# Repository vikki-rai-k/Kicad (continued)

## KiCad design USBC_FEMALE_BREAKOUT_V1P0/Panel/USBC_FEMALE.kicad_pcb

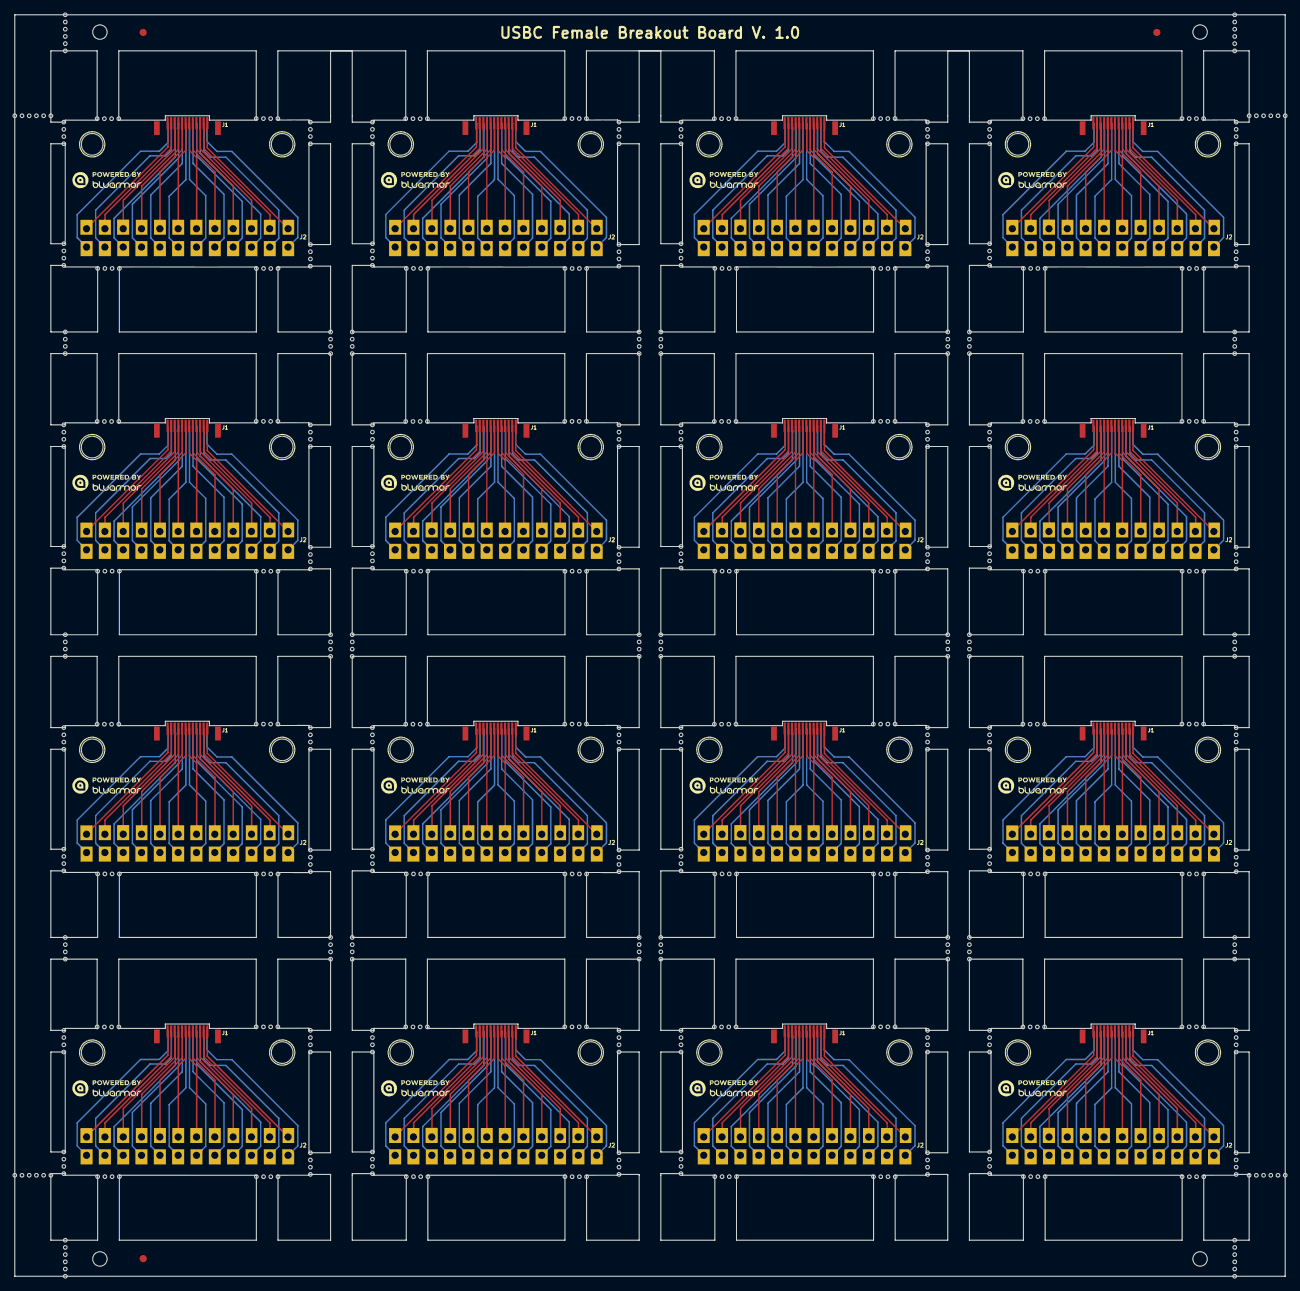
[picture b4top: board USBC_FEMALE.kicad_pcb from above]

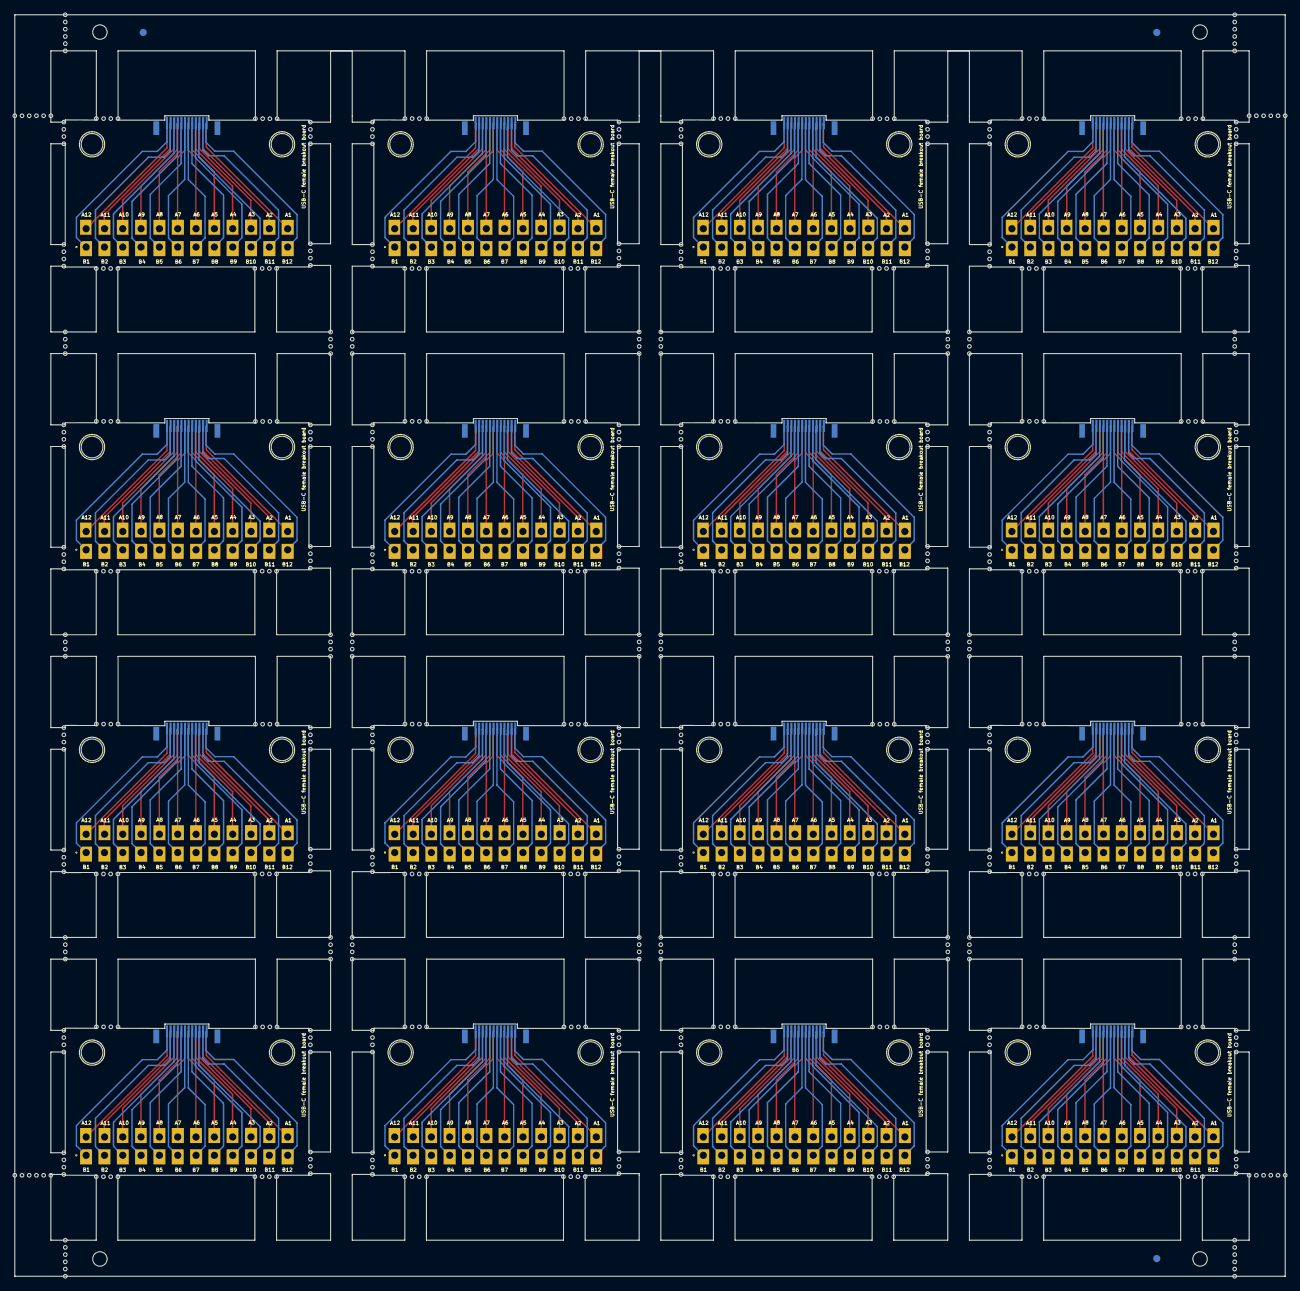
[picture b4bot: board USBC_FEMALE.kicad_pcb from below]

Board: 2 copper layers, 176.1 x 174.9 mm, 730 parts (19 on the bottom side), 384 nets.

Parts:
H1, H1#2, H1#3, H1#4, H1#5, H1#6, H1#7, H1#8, H1#9, H1#10, H1#11, H1#12, H1#13, H1#14, H1#15, H1#16, H2, H2#2, H2#3, H2#4, H2#5, H2#6, H2#7, H2#8, H2#9, H2#10, H2#11, H2#12, H2#13, H2#14, H2#15, H2#16: MountingHoleCircle; MountingHole_Circle_3.0mm
J1, J1#2, J1#3, J1#4, J1#5, J1#6, J1#7, J1#8, J1#9, J1#10, J1#11, J1#12, J1#13, J1#14, J1#15, J1#16: 2305018-2; SHOUHAN 24PIN 0.8 L9.3 027
J2, J2#2, J2#3, J2#4, J2#5, J2#6, J2#7, J2#8, J2#9, J2#10, J2#11, J2#12, J2#13, J2#14, J2#15, J2#16: Conn_01x24; M20-97412XX_large_pads
KiKit_FID_B_1, KiKit_FID_B_2, KiKit_FID_B_3: Fiducial
KiKit_FID_T_1, KiKit_FID_T_2, KiKit_FID_T_3: Fiducial
KiKit_MB_1_1, KiKit_MB_1_2, KiKit_MB_1_3, KiKit_MB_1_4, KiKit_MB_2_1, KiKit_MB_2_2, KiKit_MB_2_3, KiKit_MB_2_4, KiKit_MB_3_1, KiKit_MB_3_2, KiKit_MB_3_3, KiKit_MB_3_4, KiKit_MB_4_1, KiKit_MB_4_2, KiKit_MB_4_3, KiKit_MB_4_4, KiKit_MB_5_1, KiKit_MB_5_2, KiKit_MB_5_3, KiKit_MB_5_4, KiKit_MB_6_1, KiKit_MB_6_2, KiKit_MB_6_3, KiKit_MB_6_4, KiKit_MB_7_1, KiKit_MB_7_2, KiKit_MB_7_3, KiKit_MB_7_4, KiKit_MB_8_1, KiKit_MB_8_2, KiKit_MB_8_3, KiKit_MB_8_4, KiKit_MB_9_1, KiKit_MB_9_2, KiKit_MB_9_3, KiKit_MB_9_4, KiKit_MB_10_1, KiKit_MB_10_2, KiKit_MB_10_3, KiKit_MB_10_4, KiKit_MB_11_1, KiKit_MB_11_2, KiKit_MB_11_3, KiKit_MB_11_4, KiKit_MB_12_1, KiKit_MB_12_2, KiKit_MB_12_3, KiKit_MB_12_4, KiKit_MB_13_1, KiKit_MB_13_2, KiKit_MB_13_3, KiKit_MB_13_4, KiKit_MB_14_1, KiKit_MB_14_2, KiKit_MB_14_3, KiKit_MB_14_4, KiKit_MB_15_1, KiKit_MB_15_2, KiKit_MB_15_3, KiKit_MB_15_4, KiKit_MB_16_1, KiKit_MB_16_2, KiKit_MB_16_3, KiKit_MB_16_4, KiKit_MB_17_1, KiKit_MB_17_2, KiKit_MB_17_3, KiKit_MB_17_4, KiKit_MB_18_1, KiKit_MB_18_2, KiKit_MB_18_3, KiKit_MB_18_4, KiKit_MB_19_1, KiKit_MB_19_2, KiKit_MB_19_3, KiKit_MB_19_4, KiKit_MB_20_1, KiKit_MB_20_2, KiKit_MB_20_3, KiKit_MB_20_4, KiKit_MB_21_1, KiKit_MB_21_2, KiKit_MB_21_3, KiKit_MB_21_4, KiKit_MB_22_1, KiKit_MB_22_2, KiKit_MB_22_3, KiKit_MB_22_4, KiKit_MB_23_1, KiKit_MB_23_2, KiKit_MB_23_3, KiKit_MB_23_4, KiKit_MB_24_1, KiKit_MB_24_2, KiKit_MB_24_3, KiKit_MB_24_4, KiKit_MB_25_1, KiKit_MB_25_2, KiKit_MB_25_3, KiKit_MB_25_4, KiKit_MB_26_1, KiKit_MB_26_2, KiKit_MB_26_3, KiKit_MB_26_4, KiKit_MB_27_1, KiKit_MB_27_2, KiKit_MB_27_3, KiKit_MB_27_4, KiKit_MB_28_1, KiKit_MB_28_2, KiKit_MB_28_3, KiKit_MB_28_4, KiKit_MB_29_1, KiKit_MB_29_2, KiKit_MB_29_3, KiKit_MB_29_4, KiKit_MB_30_1, KiKit_MB_30_2, KiKit_MB_30_3, KiKit_MB_30_4, KiKit_MB_31_1, KiKit_MB_31_2, KiKit_MB_31_3, KiKit_MB_31_4, KiKit_MB_32_1, KiKit_MB_32_2, KiKit_MB_32_3, KiKit_MB_32_4, KiKit_MB_33_1, KiKit_MB_33_2, KiKit_MB_33_3, KiKit_MB_33_4, KiKit_MB_34_1, KiKit_MB_34_2, KiKit_MB_34_3, KiKit_MB_34_4, KiKit_MB_35_1, KiKit_MB_35_2, KiKit_MB_35_3, KiKit_MB_35_4, KiKit_MB_36_1, KiKit_MB_36_2, KiKit_MB_36_3, KiKit_MB_36_4, KiKit_MB_37_1, KiKit_MB_37_2, KiKit_MB_37_3, KiKit_MB_37_4, KiKit_MB_38_1, KiKit_MB_38_2, KiKit_MB_38_3, KiKit_MB_38_4, KiKit_MB_39_1, KiKit_MB_39_2, KiKit_MB_39_3, KiKit_MB_39_4, KiKit_MB_40_1, KiKit_MB_40_2, KiKit_MB_40_3, KiKit_MB_40_4, KiKit_MB_41_1, KiKit_MB_41_2, KiKit_MB_41_3, KiKit_MB_41_4, KiKit_MB_42_1, KiKit_MB_42_2, KiKit_MB_42_3, KiKit_MB_42_4, KiKit_MB_43_1, KiKit_MB_43_2, KiKit_MB_43_3, KiKit_MB_43_4, KiKit_MB_44_1, KiKit_MB_44_2, KiKit_MB_44_3, KiKit_MB_44_4, KiKit_MB_45_1, KiKit_MB_45_2, KiKit_MB_45_3, KiKit_MB_45_4, KiKit_MB_46_1, KiKit_MB_46_2, KiKit_MB_46_3, KiKit_MB_46_4, KiKit_MB_47_1, KiKit_MB_47_2, KiKit_MB_47_3, KiKit_MB_47_4, KiKit_MB_48_1, KiKit_MB_48_2, KiKit_MB_48_3, KiKit_MB_48_4, KiKit_MB_49_1, KiKit_MB_49_2, KiKit_MB_49_3, KiKit_MB_49_4, KiKit_MB_50_1, KiKit_MB_50_2, KiKit_MB_50_3, KiKit_MB_50_4, KiKit_MB_51_1, KiKit_MB_51_2, KiKit_MB_51_3, KiKit_MB_51_4, KiKit_MB_52_1, KiKit_MB_52_2, KiKit_MB_52_3, KiKit_MB_52_4, KiKit_MB_53_1, KiKit_MB_53_2, KiKit_MB_53_3, KiKit_MB_53_4, KiKit_MB_54_1, KiKit_MB_54_2, KiKit_MB_54_3, KiKit_MB_54_4, KiKit_MB_55_1, KiKit_MB_55_2, KiKit_MB_55_3, KiKit_MB_55_4, KiKit_MB_56_1, KiKit_MB_56_2, KiKit_MB_56_3, KiKit_MB_56_4, KiKit_MB_57_1, KiKit_MB_57_2, KiKit_MB_57_3, KiKit_MB_57_4, KiKit_MB_58_1, KiKit_MB_58_2, KiKit_MB_58_3, KiKit_MB_58_4, KiKit_MB_59_1, KiKit_MB_59_2, KiKit_MB_59_3, KiKit_MB_59_4, KiKit_MB_60_1, KiKit_MB_60_2, KiKit_MB_60_3, KiKit_MB_60_4, KiKit_MB_61_1, KiKit_MB_61_2, KiKit_MB_61_3, KiKit_MB_61_4, KiKit_MB_62_1, KiKit_MB_62_2, KiKit_MB_62_3, KiKit_MB_62_4, KiKit_MB_63_1, KiKit_MB_63_2, KiKit_MB_63_3, KiKit_MB_63_4, KiKit_MB_64_1, KiKit_MB_64_2, KiKit_MB_64_3, KiKit_MB_64_4, KiKit_MB_65_1, KiKit_MB_65_2, KiKit_MB_65_3, KiKit_MB_65_4, KiKit_MB_66_1, KiKit_MB_66_2, KiKit_MB_66_3, KiKit_MB_66_4, KiKit_MB_67_1, KiKit_MB_67_2, KiKit_MB_67_3, KiKit_MB_67_4, KiKit_MB_68_1, KiKit_MB_68_2, KiKit_MB_68_3, KiKit_MB_68_4, KiKit_MB_69_1, KiKit_MB_69_2, KiKit_MB_69_3, KiKit_MB_69_4, KiKit_MB_70_1, KiKit_MB_70_2, KiKit_MB_70_3, KiKit_MB_70_4, KiKit_MB_71_1, KiKit_MB_71_2, KiKit_MB_71_3, KiKit_MB_71_4, KiKit_MB_72_1, KiKit_MB_72_2, KiKit_MB_72_3, KiKit_MB_72_4, KiKit_MB_73_1, KiKit_MB_73_2, KiKit_MB_73_3, KiKit_MB_73_4, KiKit_MB_74_1, KiKit_MB_74_2, KiKit_MB_74_3, KiKit_MB_74_4, KiKit_MB_75_1, KiKit_MB_75_2, KiKit_MB_75_3, KiKit_MB_75_4, KiKit_MB_76_1, KiKit_MB_76_2, KiKit_MB_76_3, KiKit_MB_76_4, KiKit_MB_77_1, KiKit_MB_77_2, KiKit_MB_77_3, KiKit_MB_77_4, KiKit_MB_78_1, KiKit_MB_78_2, KiKit_MB_78_3, KiKit_MB_78_4, KiKit_MB_79_1, KiKit_MB_79_2, KiKit_MB_79_3, KiKit_MB_79_4, KiKit_MB_80_1, KiKit_MB_80_2, KiKit_MB_80_3, KiKit_MB_80_4, KiKit_MB_81_1, KiKit_MB_81_2, KiKit_MB_81_3, KiKit_MB_81_4, KiKit_MB_82_1, KiKit_MB_82_2, KiKit_MB_82_3, KiKit_MB_82_4, KiKit_MB_83_1, KiKit_MB_83_2, KiKit_MB_83_3, KiKit_MB_83_4, KiKit_MB_84_1, KiKit_MB_84_2, KiKit_MB_84_3, KiKit_MB_84_4, KiKit_MB_85_1, KiKit_MB_85_2, KiKit_MB_85_3, KiKit_MB_85_4, KiKit_MB_86_1, KiKit_MB_86_2, KiKit_MB_86_3, KiKit_MB_86_4, KiKit_MB_87_1, KiKit_MB_87_2, KiKit_MB_87_3, KiKit_MB_87_4, KiKit_MB_88_1, KiKit_MB_88_2, KiKit_MB_88_3, KiKit_MB_88_4, KiKit_MB_89_1, KiKit_MB_89_2, KiKit_MB_89_3, KiKit_MB_89_4, KiKit_MB_90_1, KiKit_MB_90_2, KiKit_MB_90_3, KiKit_MB_90_4, KiKit_MB_91_1, KiKit_MB_91_2, KiKit_MB_91_3, KiKit_MB_91_4, KiKit_MB_92_1, KiKit_MB_92_2, KiKit_MB_92_3, KiKit_MB_92_4, KiKit_MB_93_1, KiKit_MB_93_2, KiKit_MB_93_3, KiKit_MB_93_4, KiKit_MB_94_1, KiKit_MB_94_2, KiKit_MB_94_3, KiKit_MB_94_4, KiKit_MB_95_1, KiKit_MB_95_2, KiKit_MB_95_3, KiKit_MB_95_4, KiKit_MB_96_1, KiKit_MB_96_2, KiKit_MB_96_3, KiKit_MB_96_4, KiKit_MB_97_1, KiKit_MB_97_2, KiKit_MB_97_3, KiKit_MB_97_4, KiKit_MB_98_1, KiKit_MB_98_2, KiKit_MB_98_3, KiKit_MB_98_4, KiKit_MB_99_1, KiKit_MB_99_2, KiKit_MB_99_3, KiKit_MB_99_4, KiKit_MB_100_1, KiKit_MB_100_2, KiKit_MB_100_3, KiKit_MB_100_4, KiKit_MB_101_1, KiKit_MB_101_2, KiKit_MB_101_3, KiKit_MB_101_4, KiKit_MB_102_1, KiKit_MB_102_2, KiKit_MB_102_3, KiKit_MB_102_4, KiKit_MB_103_1, KiKit_MB_103_2, KiKit_MB_103_3, KiKit_MB_103_4, KiKit_MB_104_1, KiKit_MB_104_2, KiKit_MB_104_3, KiKit_MB_104_4, KiKit_MB_105_1, KiKit_MB_105_2, KiKit_MB_105_3, KiKit_MB_105_4, KiKit_MB_106_1, KiKit_MB_106_2, KiKit_MB_106_3, KiKit_MB_106_4, KiKit_MB_107_1, KiKit_MB_107_2, KiKit_MB_107_3, KiKit_MB_107_4, KiKit_MB_108_1, KiKit_MB_108_2, KiKit_MB_108_3, KiKit_MB_108_4, KiKit_MB_109_1, KiKit_MB_109_2, KiKit_MB_109_3, KiKit_MB_109_4, KiKit_MB_110_1, KiKit_MB_110_2, KiKit_MB_110_3, KiKit_MB_110_4, KiKit_MB_111_1, KiKit_MB_111_2, KiKit_MB_111_3, KiKit_MB_111_4, KiKit_MB_112_1, KiKit_MB_112_2, KiKit_MB_112_3, KiKit_MB_112_4, KiKit_MB_113_1, KiKit_MB_113_2, KiKit_MB_113_3, KiKit_MB_113_4, KiKit_MB_114_1, KiKit_MB_114_2, KiKit_MB_114_3, KiKit_MB_114_4, KiKit_MB_115_1, KiKit_MB_115_2, KiKit_MB_115_3, KiKit_MB_115_4, KiKit_MB_116_1, KiKit_MB_116_2, KiKit_MB_116_3, KiKit_MB_116_4, KiKit_MB_117_1, KiKit_MB_117_2, KiKit_MB_117_3, KiKit_MB_117_4, KiKit_MB_118_1, KiKit_MB_118_2, KiKit_MB_118_3, KiKit_MB_118_4, KiKit_MB_119_1, KiKit_MB_119_2, KiKit_MB_119_3, KiKit_MB_119_4, KiKit_MB_120_1, KiKit_MB_120_2, KiKit_MB_120_3, KiKit_MB_120_4, KiKit_MB_121_1, KiKit_MB_121_2, KiKit_MB_121_3, KiKit_MB_121_4, KiKit_MB_122_1, KiKit_MB_122_2, KiKit_MB_122_3, KiKit_MB_122_4, KiKit_MB_123_1, KiKit_MB_123_2, KiKit_MB_123_3, KiKit_MB_123_4, KiKit_MB_124_1, KiKit_MB_124_2, KiKit_MB_124_3, KiKit_MB_124_4, KiKit_MB_125_1, KiKit_MB_125_2, KiKit_MB_125_3, KiKit_MB_125_4, KiKit_MB_126_1, KiKit_MB_126_2, KiKit_MB_126_3, KiKit_MB_126_4, KiKit_MB_127_1, KiKit_MB_127_2, KiKit_MB_127_3, KiKit_MB_127_4, KiKit_MB_128_1, KiKit_MB_128_2, KiKit_MB_128_3, KiKit_MB_128_4, KiKit_MB_129_1, KiKit_MB_129_2, KiKit_MB_129_3, KiKit_MB_129_4, KiKit_MB_130_1, KiKit_MB_130_2, KiKit_MB_130_3, KiKit_MB_130_4, KiKit_MB_131_1, KiKit_MB_131_2, KiKit_MB_131_3, KiKit_MB_131_4, KiKit_MB_132_1, KiKit_MB_132_2, KiKit_MB_132_3, KiKit_MB_132_4, KiKit_MB_133_1, KiKit_MB_133_2, KiKit_MB_133_3, KiKit_MB_133_4, KiKit_MB_134_1, KiKit_MB_134_2, KiKit_MB_134_3, KiKit_MB_134_4, KiKit_MB_135_1, KiKit_MB_135_2, KiKit_MB_135_3, KiKit_MB_135_4, KiKit_MB_136_1, KiKit_MB_136_2, KiKit_MB_136_3, KiKit_MB_136_4, KiKit_MB_137_1, KiKit_MB_137_2, KiKit_MB_137_3, KiKit_MB_137_4, KiKit_MB_138_1, KiKit_MB_138_2, KiKit_MB_138_3, KiKit_MB_138_4, KiKit_MB_139_1, KiKit_MB_139_2, KiKit_MB_139_3, KiKit_MB_139_4, KiKit_MB_140_1, KiKit_MB_140_2, KiKit_MB_140_3, KiKit_MB_140_4, KiKit_MB_141_1, KiKit_MB_141_2, KiKit_MB_141_3, KiKit_MB_141_4, KiKit_MB_142_1, KiKit_MB_142_2, KiKit_MB_142_3, KiKit_MB_142_4, KiKit_MB_143_1, KiKit_MB_143_2, KiKit_MB_143_3, KiKit_MB_143_4, KiKit_MB_144_1, KiKit_MB_144_2, KiKit_MB_144_3, KiKit_MB_144_4, KiKit_MB_145_1, KiKit_MB_145_2, KiKit_MB_145_3, KiKit_MB_145_4, KiKit_MB_146_1, KiKit_MB_146_2, KiKit_MB_146_3, KiKit_MB_146_4, KiKit_MB_147_1, KiKit_MB_147_2, KiKit_MB_147_3, KiKit_MB_147_4, KiKit_MB_148_1, KiKit_MB_148_2, KiKit_MB_148_3, KiKit_MB_148_4, KiKit_MB_149_1, KiKit_MB_149_2, KiKit_MB_149_3, KiKit_MB_149_4, KiKit_MB_150_1, KiKit_MB_150_2, KiKit_MB_150_3, KiKit_MB_150_4, KiKit_MB_151_1, KiKit_MB_151_2, KiKit_MB_151_3, KiKit_MB_151_4, KiKit_MB_152_1, KiKit_MB_152_2, KiKit_MB_152_3, KiKit_MB_152_4, KiKit_MB_153_1, KiKit_MB_153_2, KiKit_MB_153_3, KiKit_MB_153_4, KiKit_MB_153_5, KiKit_MB_153_6, KiKit_MB_154_1, KiKit_MB_154_2, KiKit_MB_154_3, KiKit_MB_154_4, KiKit_MB_154_5, KiKit_MB_154_6, KiKit_MB_155_1, KiKit_MB_155_2, KiKit_MB_155_3, KiKit_MB_155_4, KiKit_MB_155_5, KiKit_MB_155_6, KiKit_MB_156_1, KiKit_MB_156_2, KiKit_MB_156_3, KiKit_MB_156_4, KiKit_MB_156_5, KiKit_MB_156_6, KiKit_MB_157_1, KiKit_MB_157_2, KiKit_MB_157_3, KiKit_MB_157_4, KiKit_MB_157_5, KiKit_MB_157_6, KiKit_MB_158_1, KiKit_MB_158_2, KiKit_MB_158_3, KiKit_MB_158_4, KiKit_MB_158_5, KiKit_MB_158_6, KiKit_MB_159_1, KiKit_MB_159_2, KiKit_MB_159_3, KiKit_MB_159_4, KiKit_MB_159_5, KiKit_MB_159_6, KiKit_MB_160_1, KiKit_MB_160_2, KiKit_MB_160_3, KiKit_MB_160_4, KiKit_MB_160_5, KiKit_MB_160_6: NPTH
KiKit_TO_1, KiKit_TO_2, KiKit_TO_3, KiKit_TO_4: NPTH

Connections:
Board_0-/A1: J1#3.A1 (GNDA), J2#6.24
Board_0-/A2: J1#3.A2 (TX1_P), J2#6.22
Board_0-/A3: J1#3.A3 (TX1_N), J2#6.20
Board_0-/A4: J1#3.A4 (VBUS_A), J2#6.18
Board_0-/A5: J1#3.A5 (CC1), J2#6.16
Board_0-/A6: J1#3.A6 (DA_P), J2#6.14
Board_0-/A7: J1#3.A7 (DA_N), J2#6.12
Board_0-/A8: J1#3.A8 (SBU1), J2#6.10
Board_0-/A9: J1#3.A9 (VBUS_A), J2#6.8
Board_0-/A10: J1#3.A10 (RX2_N), J2#6.6
Board_0-/A11: J1#3.A11 (RX2_P), J2#6.4
Board_0-/A12: J1#3.A12 (GNDA), J2#6.2
Board_0-/B1: J1#3.B1 (GNDB), J2#6.1
Board_0-/B2: J1#3.B2 (TX2_P), J2#6.3
Board_0-/B3: J1#3.B3 (TX2_N), J2#6.5
Board_0-/B4: J1#3.B4 (VBUS_B), J2#6.7
Board_0-/B5: J1#3.B5 (CC2), J2#6.9
Board_0-/B6: J1#3.B6 (DB_P), J2#6.11
Board_0-/B7: J1#3.B7 (DB_N), J2#6.13
Board_0-/B8: J1#3.B8 (SBU2), J2#6.15
Board_0-/B9: J1#3.B9 (VBUS_B), J2#6.17
Board_0-/B10: J1#3.B10 (RX1_N), J2#6.19
Board_0-/B11: J1#3.B11 (RX1_P), J2#6.21
Board_0-/B12: J1#3.B12 (GNDB), J2#6.23
Board_1-/A1: J1#12.A1 (GNDA), J2#4.24
Board_1-/A2: J1#12.A2 (TX1_P), J2#4.22
Board_1-/A3: J1#12.A3 (TX1_N), J2#4.20
Board_1-/A4: J1#12.A4 (VBUS_A), J2#4.18
Board_1-/A5: J1#12.A5 (CC1), J2#4.16
Board_1-/A6: J1#12.A6 (DA_P), J2#4.14
Board_1-/A7: J1#12.A7 (DA_N), J2#4.12
Board_1-/A8: J1#12.A8 (SBU1), J2#4.10
Board_1-/A9: J1#12.A9 (VBUS_A), J2#4.8
Board_1-/A10: J1#12.A10 (RX2_N), J2#4.6
Board_1-/A11: J1#12.A11 (RX2_P), J2#4.4
Board_1-/A12: J1#12.A12 (GNDA), J2#4.2
Board_1-/B1: J1#12.B1 (GNDB), J2#4.1
Board_1-/B2: J1#12.B2 (TX2_P), J2#4.3
Board_1-/B3: J1#12.B3 (TX2_N), J2#4.5
Board_1-/B4: J1#12.B4 (VBUS_B), J2#4.7
Board_1-/B5: J1#12.B5 (CC2), J2#4.9
Board_1-/B6: J1#12.B6 (DB_P), J2#4.11
Board_1-/B7: J1#12.B7 (DB_N), J2#4.13
Board_1-/B8: J1#12.B8 (SBU2), J2#4.15
Board_1-/B9: J1#12.B9 (VBUS_B), J2#4.17
Board_1-/B10: J1#12.B10 (RX1_N), J2#4.19
Board_1-/B11: J1#12.B11 (RX1_P), J2#4.21
Board_1-/B12: J1#12.B12 (GNDB), J2#4.23
Board_2-/A1: J1#15.A1 (GNDA), J2#7.24
Board_2-/A2: J1#15.A2 (TX1_P), J2#7.22
Board_2-/A3: J1#15.A3 (TX1_N), J2#7.20
Board_2-/A4: J1#15.A4 (VBUS_A), J2#7.18
Board_2-/A5: J1#15.A5 (CC1), J2#7.16
Board_2-/A6: J1#15.A6 (DA_P), J2#7.14
Board_2-/A7: J1#15.A7 (DA_N), J2#7.12
Board_2-/A8: J1#15.A8 (SBU1), J2#7.10
Board_2-/A9: J1#15.A9 (VBUS_A), J2#7.8
Board_2-/A10: J1#15.A10 (RX2_N), J2#7.6
Board_2-/A11: J1#15.A11 (RX2_P), J2#7.4
Board_2-/A12: J1#15.A12 (GNDA), J2#7.2
Board_2-/B1: J1#15.B1 (GNDB), J2#7.1
Board_2-/B2: J1#15.B2 (TX2_P), J2#7.3
Board_2-/B3: J1#15.B3 (TX2_N), J2#7.5
Board_2-/B4: J1#15.B4 (VBUS_B), J2#7.7
Board_2-/B5: J1#15.B5 (CC2), J2#7.9
Board_2-/B6: J1#15.B6 (DB_P), J2#7.11
Board_2-/B7: J1#15.B7 (DB_N), J2#7.13
Board_2-/B8: J1#15.B8 (SBU2), J2#7.15
Board_2-/B9: J1#15.B9 (VBUS_B), J2#7.17
Board_2-/B10: J1#15.B10 (RX1_N), J2#7.19
Board_2-/B11: J1#15.B11 (RX1_P), J2#7.21
Board_2-/B12: J1#15.B12 (GNDB), J2#7.23
Board_3-/A1: J1#7.A1 (GNDA), J2#10.24
Board_3-/A2: J1#7.A2 (TX1_P), J2#10.22
Board_3-/A3: J1#7.A3 (TX1_N), J2#10.20
Board_3-/A4: J1#7.A4 (VBUS_A), J2#10.18
Board_3-/A5: J1#7.A5 (CC1), J2#10.16
Board_3-/A6: J1#7.A6 (DA_P), J2#10.14
Board_3-/A7: J1#7.A7 (DA_N), J2#10.12
Board_3-/A8: J1#7.A8 (SBU1), J2#10.10
Board_3-/A9: J1#7.A9 (VBUS_A), J2#10.8
Board_3-/A10: J1#7.A10 (RX2_N), J2#10.6
Board_3-/A11: J1#7.A11 (RX2_P), J2#10.4
Board_3-/A12: J1#7.A12 (GNDA), J2#10.2
Board_3-/B1: J1#7.B1 (GNDB), J2#10.1
Board_3-/B2: J1#7.B2 (TX2_P), J2#10.3
Board_3-/B3: J1#7.B3 (TX2_N), J2#10.5
Board_3-/B4: J1#7.B4 (VBUS_B), J2#10.7
Board_3-/B5: J1#7.B5 (CC2), J2#10.9
Board_3-/B6: J1#7.B6 (DB_P), J2#10.11
Board_3-/B7: J1#7.B7 (DB_N), J2#10.13
Board_3-/B8: J1#7.B8 (SBU2), J2#10.15
Board_3-/B9: J1#7.B9 (VBUS_B), J2#10.17
Board_3-/B10: J1#7.B10 (RX1_N), J2#10.19
Board_3-/B11: J1#7.B11 (RX1_P), J2#10.21
Board_3-/B12: J1#7.B12 (GNDB), J2#10.23
Board_4-/A1: J1#5.A1 (GNDA), J2#9.24
Board_4-/A2: J1#5.A2 (TX1_P), J2#9.22
Board_4-/A3: J1#5.A3 (TX1_N), J2#9.20
Board_4-/A4: J1#5.A4 (VBUS_A), J2#9.18
Board_4-/A5: J1#5.A5 (CC1), J2#9.16
Board_4-/A6: J1#5.A6 (DA_P), J2#9.14
Board_4-/A7: J1#5.A7 (DA_N), J2#9.12
Board_4-/A8: J1#5.A8 (SBU1), J2#9.10
Board_4-/A9: J1#5.A9 (VBUS_A), J2#9.8
Board_4-/A10: J1#5.A10 (RX2_N), J2#9.6
Board_4-/A11: J1#5.A11 (RX2_P), J2#9.4
Board_4-/A12: J1#5.A12 (GNDA), J2#9.2
Board_4-/B1: J1#5.B1 (GNDB), J2#9.1
Board_4-/B2: J1#5.B2 (TX2_P), J2#9.3
Board_4-/B3: J1#5.B3 (TX2_N), J2#9.5
Board_4-/B4: J1#5.B4 (VBUS_B), J2#9.7
Board_4-/B5: J1#5.B5 (CC2), J2#9.9
Board_4-/B6: J1#5.B6 (DB_P), J2#9.11
Board_4-/B7: J1#5.B7 (DB_N), J2#9.13
Board_4-/B8: J1#5.B8 (SBU2), J2#9.15
Board_4-/B9: J1#5.B9 (VBUS_B), J2#9.17
Board_4-/B10: J1#5.B10 (RX1_N), J2#9.19
Board_4-/B11: J1#5.B11 (RX1_P), J2#9.21
Board_4-/B12: J1#5.B12 (GNDB), J2#9.23
Board_5-/A1: J1#8.A1 (GNDA), J2#2.24
Board_5-/A2: J1#8.A2 (TX1_P), J2#2.22
Board_5-/A3: J1#8.A3 (TX1_N), J2#2.20
Board_5-/A4: J1#8.A4 (VBUS_A), J2#2.18
Board_5-/A5: J1#8.A5 (CC1), J2#2.16
Board_5-/A6: J1#8.A6 (DA_P), J2#2.14
Board_5-/A7: J1#8.A7 (DA_N), J2#2.12
Board_5-/A8: J1#8.A8 (SBU1), J2#2.10
Board_5-/A9: J1#8.A9 (VBUS_A), J2#2.8
Board_5-/A10: J1#8.A10 (RX2_N), J2#2.6
Board_5-/A11: J1#8.A11 (RX2_P), J2#2.4
Board_5-/A12: J1#8.A12 (GNDA), J2#2.2
Board_5-/B1: J1#8.B1 (GNDB), J2#2.1
Board_5-/B2: J1#8.B2 (TX2_P), J2#2.3
Board_5-/B3: J1#8.B3 (TX2_N), J2#2.5
Board_5-/B4: J1#8.B4 (VBUS_B), J2#2.7
Board_5-/B5: J1#8.B5 (CC2), J2#2.9
Board_5-/B6: J1#8.B6 (DB_P), J2#2.11
Board_5-/B7: J1#8.B7 (DB_N), J2#2.13
Board_5-/B8: J1#8.B8 (SBU2), J2#2.15
Board_5-/B9: J1#8.B9 (VBUS_B), J2#2.17
Board_5-/B10: J1#8.B10 (RX1_N), J2#2.19
Board_5-/B11: J1#8.B11 (RX1_P), J2#2.21
Board_5-/B12: J1#8.B12 (GNDB), J2#2.23
Board_6-/A1: J1#16.A1 (GNDA), J2#13.24
Board_6-/A2: J1#16.A2 (TX1_P), J2#13.22
Board_6-/A3: J1#16.A3 (TX1_N), J2#13.20
Board_6-/A4: J1#16.A4 (VBUS_A), J2#13.18
Board_6-/A5: J1#16.A5 (CC1), J2#13.16
Board_6-/A6: J1#16.A6 (DA_P), J2#13.14
Board_6-/A7: J1#16.A7 (DA_N), J2#13.12
Board_6-/A8: J1#16.A8 (SBU1), J2#13.10
Board_6-/A9: J1#16.A9 (VBUS_A), J2#13.8
Board_6-/A10: J1#16.A10 (RX2_N), J2#13.6
Board_6-/A11: J1#16.A11 (RX2_P), J2#13.4
Board_6-/A12: J1#16.A12 (GNDA), J2#13.2
Board_6-/B1: J1#16.B1 (GNDB), J2#13.1
Board_6-/B2: J1#16.B2 (TX2_P), J2#13.3
Board_6-/B3: J1#16.B3 (TX2_N), J2#13.5
Board_6-/B4: J1#16.B4 (VBUS_B), J2#13.7
Board_6-/B5: J1#16.B5 (CC2), J2#13.9
Board_6-/B6: J1#16.B6 (DB_P), J2#13.11
Board_6-/B7: J1#16.B7 (DB_N), J2#13.13
Board_6-/B8: J1#16.B8 (SBU2), J2#13.15
Board_6-/B9: J1#16.B9 (VBUS_B), J2#13.17
Board_6-/B10: J1#16.B10 (RX1_N), J2#13.19
Board_6-/B11: J1#16.B11 (RX1_P), J2#13.21
Board_6-/B12: J1#16.B12 (GNDB), J2#13.23
Board_7-/A1: J1#9.A1 (GNDA), J2#14.24
Board_7-/A2: J1#9.A2 (TX1_P), J2#14.22
Board_7-/A3: J1#9.A3 (TX1_N), J2#14.20
Board_7-/A4: J1#9.A4 (VBUS_A), J2#14.18
Board_7-/A5: J1#9.A5 (CC1), J2#14.16
Board_7-/A6: J1#9.A6 (DA_P), J2#14.14
Board_7-/A7: J1#9.A7 (DA_N), J2#14.12
Board_7-/A8: J1#9.A8 (SBU1), J2#14.10
Board_7-/A9: J1#9.A9 (VBUS_A), J2#14.8
Board_7-/A10: J1#9.A10 (RX2_N), J2#14.6
Board_7-/A11: J1#9.A11 (RX2_P), J2#14.4
Board_7-/A12: J1#9.A12 (GNDA), J2#14.2
Board_7-/B1: J1#9.B1 (GNDB), J2#14.1
Board_7-/B2: J1#9.B2 (TX2_P), J2#14.3
Board_7-/B3: J1#9.B3 (TX2_N), J2#14.5
Board_7-/B4: J1#9.B4 (VBUS_B), J2#14.7
Board_7-/B5: J1#9.B5 (CC2), J2#14.9
Board_7-/B6: J1#9.B6 (DB_P), J2#14.11
Board_7-/B7: J1#9.B7 (DB_N), J2#14.13
Board_7-/B8: J1#9.B8 (SBU2), J2#14.15
Board_7-/B9: J1#9.B9 (VBUS_B), J2#14.17
Board_7-/B10: J1#9.B10 (RX1_N), J2#14.19
Board_7-/B11: J1#9.B11 (RX1_P), J2#14.21
Board_7-/B12: J1#9.B12 (GNDB), J2#14.23
Board_8-/A1: J1#10.A1 (GNDA), J2.24
Board_8-/A2: J1#10.A2 (TX1_P), J2.22
Board_8-/A3: J1#10.A3 (TX1_N), J2.20
Board_8-/A4: J1#10.A4 (VBUS_A), J2.18
Board_8-/A5: J1#10.A5 (CC1), J2.16
Board_8-/A6: J1#10.A6 (DA_P), J2.14
Board_8-/A7: J1#10.A7 (DA_N), J2.12
Board_8-/A8: J1#10.A8 (SBU1), J2.10
Board_8-/A9: J1#10.A9 (VBUS_A), J2.8
Board_8-/A10: J1#10.A10 (RX2_N), J2.6
Board_8-/A11: J1#10.A11 (RX2_P), J2.4
Board_8-/A12: J1#10.A12 (GNDA), J2.2
Board_8-/B1: J1#10.B1 (GNDB), J2.1
Board_8-/B2: J1#10.B2 (TX2_P), J2.3
Board_8-/B3: J1#10.B3 (TX2_N), J2.5
Board_8-/B4: J1#10.B4 (VBUS_B), J2.7
Board_8-/B5: J1#10.B5 (CC2), J2.9
Board_8-/B6: J1#10.B6 (DB_P), J2.11
Board_8-/B7: J1#10.B7 (DB_N), J2.13
Board_8-/B8: J1#10.B8 (SBU2), J2.15
Board_8-/B9: J1#10.B9 (VBUS_B), J2.17
Board_8-/B10: J1#10.B10 (RX1_N), J2.19
Board_8-/B11: J1#10.B11 (RX1_P), J2.21
Board_8-/B12: J1#10.B12 (GNDB), J2.23
Board_9-/A1: J1#14.A1 (GNDA), J2#16.24
Board_9-/A2: J1#14.A2 (TX1_P), J2#16.22
Board_9-/A3: J1#14.A3 (TX1_N), J2#16.20
Board_9-/A4: J1#14.A4 (VBUS_A), J2#16.18
Board_9-/A5: J1#14.A5 (CC1), J2#16.16
Board_9-/A6: J1#14.A6 (DA_P), J2#16.14
Board_9-/A7: J1#14.A7 (DA_N), J2#16.12
Board_9-/A8: J1#14.A8 (SBU1), J2#16.10
Board_9-/A9: J1#14.A9 (VBUS_A), J2#16.8
Board_9-/A10: J1#14.A10 (RX2_N), J2#16.6
Board_9-/A11: J1#14.A11 (RX2_P), J2#16.4
Board_9-/A12: J1#14.A12 (GNDA), J2#16.2
Board_9-/B1: J1#14.B1 (GNDB), J2#16.1
Board_9-/B2: J1#14.B2 (TX2_P), J2#16.3
Board_9-/B3: J1#14.B3 (TX2_N), J2#16.5
Board_9-/B4: J1#14.B4 (VBUS_B), J2#16.7
Board_9-/B5: J1#14.B5 (CC2), J2#16.9
Board_9-/B6: J1#14.B6 (DB_P), J2#16.11
Board_9-/B7: J1#14.B7 (DB_N), J2#16.13
Board_9-/B8: J1#14.B8 (SBU2), J2#16.15
Board_9-/B9: J1#14.B9 (VBUS_B), J2#16.17
Board_9-/B10: J1#14.B10 (RX1_N), J2#16.19
Board_9-/B11: J1#14.B11 (RX1_P), J2#16.21
Board_9-/B12: J1#14.B12 (GNDB), J2#16.23
Board_10-/A1: J1#6.A1 (GNDA), J2#15.24
Board_10-/A2: J1#6.A2 (TX1_P), J2#15.22
Board_10-/A3: J1#6.A3 (TX1_N), J2#15.20
Board_10-/A4: J1#6.A4 (VBUS_A), J2#15.18
Board_10-/A5: J1#6.A5 (CC1), J2#15.16
Board_10-/A6: J1#6.A6 (DA_P), J2#15.14
Board_10-/A7: J1#6.A7 (DA_N), J2#15.12
Board_10-/A8: J1#6.A8 (SBU1), J2#15.10
Board_10-/A9: J1#6.A9 (VBUS_A), J2#15.8
Board_10-/A10: J1#6.A10 (RX2_N), J2#15.6
Board_10-/A11: J1#6.A11 (RX2_P), J2#15.4
Board_10-/A12: J1#6.A12 (GNDA), J2#15.2
Board_10-/B1: J1#6.B1 (GNDB), J2#15.1
Board_10-/B2: J1#6.B2 (TX2_P), J2#15.3
Board_10-/B3: J1#6.B3 (TX2_N), J2#15.5
Board_10-/B4: J1#6.B4 (VBUS_B), J2#15.7
Board_10-/B5: J1#6.B5 (CC2), J2#15.9
Board_10-/B6: J1#6.B6 (DB_P), J2#15.11
Board_10-/B7: J1#6.B7 (DB_N), J2#15.13
Board_10-/B8: J1#6.B8 (SBU2), J2#15.15
Board_10-/B9: J1#6.B9 (VBUS_B), J2#15.17
Board_10-/B10: J1#6.B10 (RX1_N), J2#15.19
Board_10-/B11: J1#6.B11 (RX1_P), J2#15.21
Board_10-/B12: J1#6.B12 (GNDB), J2#15.23
Board_11-/A1: J1#2.A1 (GNDA), J2#5.24
Board_11-/A2: J1#2.A2 (TX1_P), J2#5.22
Board_11-/A3: J1#2.A3 (TX1_N), J2#5.20
Board_11-/A4: J1#2.A4 (VBUS_A), J2#5.18
Board_11-/A5: J1#2.A5 (CC1), J2#5.16
Board_11-/A6: J1#2.A6 (DA_P), J2#5.14
Board_11-/A7: J1#2.A7 (DA_N), J2#5.12
Board_11-/A8: J1#2.A8 (SBU1), J2#5.10
Board_11-/A9: J1#2.A9 (VBUS_A), J2#5.8
Board_11-/A10: J1#2.A10 (RX2_N), J2#5.6
Board_11-/A11: J1#2.A11 (RX2_P), J2#5.4
Board_11-/A12: J1#2.A12 (GNDA), J2#5.2
Board_11-/B1: J1#2.B1 (GNDB), J2#5.1
Board_11-/B2: J1#2.B2 (TX2_P), J2#5.3
Board_11-/B3: J1#2.B3 (TX2_N), J2#5.5
Board_11-/B4: J1#2.B4 (VBUS_B), J2#5.7
Board_11-/B5: J1#2.B5 (CC2), J2#5.9
Board_11-/B6: J1#2.B6 (DB_P), J2#5.11
Board_11-/B7: J1#2.B7 (DB_N), J2#5.13
Board_11-/B8: J1#2.B8 (SBU2), J2#5.15
Board_11-/B9: J1#2.B9 (VBUS_B), J2#5.17
Board_11-/B10: J1#2.B10 (RX1_N), J2#5.19
Board_11-/B11: J1#2.B11 (RX1_P), J2#5.21
Board_11-/B12: J1#2.B12 (GNDB), J2#5.23
Board_12-/A1: J1#13.A1 (GNDA), J2#8.24
Board_12-/A2: J1#13.A2 (TX1_P), J2#8.22
Board_12-/A3: J1#13.A3 (TX1_N), J2#8.20
Board_12-/A4: J1#13.A4 (VBUS_A), J2#8.18
Board_12-/A5: J1#13.A5 (CC1), J2#8.16
Board_12-/A6: J1#13.A6 (DA_P), J2#8.14
Board_12-/A7: J1#13.A7 (DA_N), J2#8.12
Board_12-/A8: J1#13.A8 (SBU1), J2#8.10
Board_12-/A9: J1#13.A9 (VBUS_A), J2#8.8
Board_12-/A10: J1#13.A10 (RX2_N), J2#8.6
Board_12-/A11: J1#13.A11 (RX2_P), J2#8.4
Board_12-/A12: J1#13.A12 (GNDA), J2#8.2
Board_12-/B1: J1#13.B1 (GNDB), J2#8.1
Board_12-/B2: J1#13.B2 (TX2_P), J2#8.3
Board_12-/B3: J1#13.B3 (TX2_N), J2#8.5
Board_12-/B4: J1#13.B4 (VBUS_B), J2#8.7
Board_12-/B5: J1#13.B5 (CC2), J2#8.9
Board_12-/B6: J1#13.B6 (DB_P), J2#8.11
Board_12-/B7: J1#13.B7 (DB_N), J2#8.13
Board_12-/B8: J1#13.B8 (SBU2), J2#8.15
Board_12-/B9: J1#13.B9 (VBUS_B), J2#8.17
Board_12-/B10: J1#13.B10 (RX1_N), J2#8.19
Board_12-/B11: J1#13.B11 (RX1_P), J2#8.21
Board_12-/B12: J1#13.B12 (GNDB), J2#8.23
Board_13-/A1: J1.A1 (GNDA), J2#11.24
Board_13-/A2: J1.A2 (TX1_P), J2#11.22
Board_13-/A3: J1.A3 (TX1_N), J2#11.20
Board_13-/A4: J1.A4 (VBUS_A), J2#11.18
Board_13-/A5: J1.A5 (CC1), J2#11.16
Board_13-/A6: J1.A6 (DA_P), J2#11.14
Board_13-/A7: J1.A7 (DA_N), J2#11.12
Board_13-/A8: J1.A8 (SBU1), J2#11.10
Board_13-/A9: J1.A9 (VBUS_A), J2#11.8
Board_13-/A10: J1.A10 (RX2_N), J2#11.6
Board_13-/A11: J1.A11 (RX2_P), J2#11.4
Board_13-/A12: J1.A12 (GNDA), J2#11.2
Board_13-/B1: J1.B1 (GNDB), J2#11.1
Board_13-/B2: J1.B2 (TX2_P), J2#11.3
Board_13-/B3: J1.B3 (TX2_N), J2#11.5
Board_13-/B4: J1.B4 (VBUS_B), J2#11.7
Board_13-/B5: J1.B5 (CC2), J2#11.9
Board_13-/B6: J1.B6 (DB_P), J2#11.11
Board_13-/B7: J1.B7 (DB_N), J2#11.13
Board_13-/B8: J1.B8 (SBU2), J2#11.15
Board_13-/B9: J1.B9 (VBUS_B), J2#11.17
Board_13-/B10: J1.B10 (RX1_N), J2#11.19
Board_13-/B11: J1.B11 (RX1_P), J2#11.21
Board_13-/B12: J1.B12 (GNDB), J2#11.23
Board_14-/A1: J1#11.A1 (GNDA), J2#12.24
Board_14-/A2: J1#11.A2 (TX1_P), J2#12.22
Board_14-/A3: J1#11.A3 (TX1_N), J2#12.20
Board_14-/A4: J1#11.A4 (VBUS_A), J2#12.18
Board_14-/A5: J1#11.A5 (CC1), J2#12.16
Board_14-/A6: J1#11.A6 (DA_P), J2#12.14
Board_14-/A7: J1#11.A7 (DA_N), J2#12.12
Board_14-/A8: J1#11.A8 (SBU1), J2#12.10
Board_14-/A9: J1#11.A9 (VBUS_A), J2#12.8
Board_14-/A10: J1#11.A10 (RX2_N), J2#12.6
Board_14-/A11: J1#11.A11 (RX2_P), J2#12.4
Board_14-/A12: J1#11.A12 (GNDA), J2#12.2
Board_14-/B1: J1#11.B1 (GNDB), J2#12.1
Board_14-/B2: J1#11.B2 (TX2_P), J2#12.3
Board_14-/B3: J1#11.B3 (TX2_N), J2#12.5
Board_14-/B4: J1#11.B4 (VBUS_B), J2#12.7
Board_14-/B5: J1#11.B5 (CC2), J2#12.9
Board_14-/B6: J1#11.B6 (DB_P), J2#12.11
Board_14-/B7: J1#11.B7 (DB_N), J2#12.13
Board_14-/B8: J1#11.B8 (SBU2), J2#12.15
Board_14-/B9: J1#11.B9 (VBUS_B), J2#12.17
Board_14-/B10: J1#11.B10 (RX1_N), J2#12.19
Board_14-/B11: J1#11.B11 (RX1_P), J2#12.21
Board_14-/B12: J1#11.B12 (GNDB), J2#12.23
Board_15-/A1: J1#4.A1 (GNDA), J2#3.24
Board_15-/A2: J1#4.A2 (TX1_P), J2#3.22
Board_15-/A3: J1#4.A3 (TX1_N), J2#3.20
Board_15-/A4: J1#4.A4 (VBUS_A), J2#3.18
Board_15-/A5: J1#4.A5 (CC1), J2#3.16
Board_15-/A6: J1#4.A6 (DA_P), J2#3.14
Board_15-/A7: J1#4.A7 (DA_N), J2#3.12
Board_15-/A8: J1#4.A8 (SBU1), J2#3.10
Board_15-/A9: J1#4.A9 (VBUS_A), J2#3.8
Board_15-/A10: J1#4.A10 (RX2_N), J2#3.6
Board_15-/A11: J1#4.A11 (RX2_P), J2#3.4
Board_15-/A12: J1#4.A12 (GNDA), J2#3.2
Board_15-/B1: J1#4.B1 (GNDB), J2#3.1
Board_15-/B2: J1#4.B2 (TX2_P), J2#3.3
Board_15-/B3: J1#4.B3 (TX2_N), J2#3.5
Board_15-/B4: J1#4.B4 (VBUS_B), J2#3.7
Board_15-/B5: J1#4.B5 (CC2), J2#3.9
Board_15-/B6: J1#4.B6 (DB_P), J2#3.11
Board_15-/B7: J1#4.B7 (DB_N), J2#3.13
Board_15-/B8: J1#4.B8 (SBU2), J2#3.15
Board_15-/B9: J1#4.B9 (VBUS_B), J2#3.17
Board_15-/B10: J1#4.B10 (RX1_N), J2#3.19
Board_15-/B11: J1#4.B11 (RX1_P), J2#3.21
Board_15-/B12: J1#4.B12 (GNDB), J2#3.23

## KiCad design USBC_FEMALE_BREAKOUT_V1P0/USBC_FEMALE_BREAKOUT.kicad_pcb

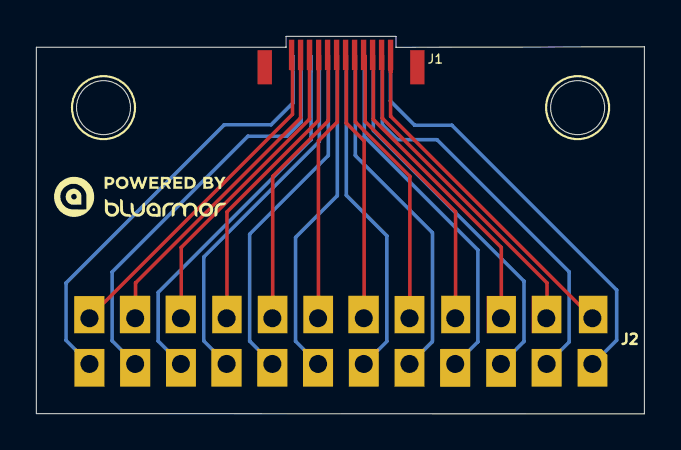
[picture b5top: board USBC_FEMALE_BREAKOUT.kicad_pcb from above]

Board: 2 copper layers, 33.8 x 21.0 mm, 4 parts (1 on the bottom side), 24 nets.

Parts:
H1, H2: MountingHoleCircle; MountingHole_Circle_3.0mm
J1: 2305018-2; SHOUHAN 24PIN 0.8 L9.3 027
J2: Conn_01x24; M20-97412XX_large_pads

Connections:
/A1: J1.A1 (GNDA), J2.24
/A2: J1.A2 (TX1_P), J2.22
/A3: J1.A3 (TX1_N), J2.20
/A4: J1.A4 (VBUS_A), J2.18
/A5: J1.A5 (CC1), J2.16
/A6: J1.A6 (DA_P), J2.14
/A7: J1.A7 (DA_N), J2.12
/A8: J1.A8 (SBU1), J2.10
/A9: J1.A9 (VBUS_A), J2.8
/A10: J1.A10 (RX2_N), J2.6
/A11: J1.A11 (RX2_P), J2.4
/A12: J1.A12 (GNDA), J2.2
/B1: J1.B1 (GNDB), J2.1
/B2: J1.B2 (TX2_P), J2.3
/B3: J1.B3 (TX2_N), J2.5
/B4: J1.B4 (VBUS_B), J2.7
/B5: J1.B5 (CC2), J2.9
/B6: J1.B6 (DB_P), J2.11
/B7: J1.B7 (DB_N), J2.13
/B8: J1.B8 (SBU2), J2.15
/B9: J1.B9 (VBUS_B), J2.17
/B10: J1.B10 (RX1_N), J2.19
/B11: J1.B11 (RX1_P), J2.21
/B12: J1.B12 (GNDB), J2.23
